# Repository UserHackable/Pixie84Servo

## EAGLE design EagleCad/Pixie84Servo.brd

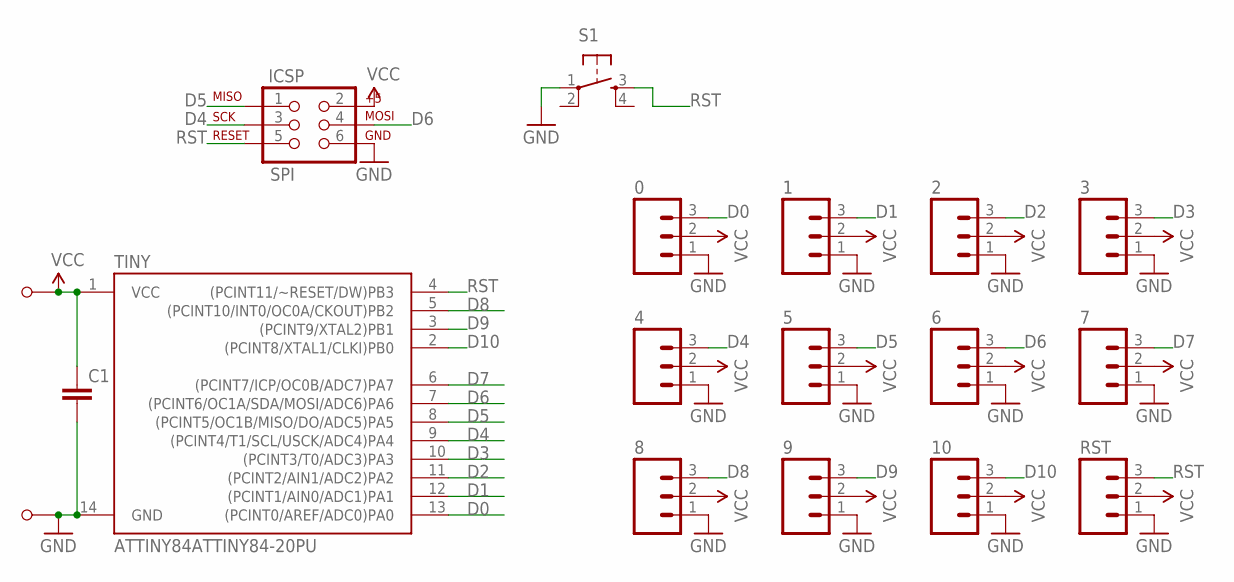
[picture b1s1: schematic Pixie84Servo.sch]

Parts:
0, 1, 2, 3, 4, 5, 6, 7, 8, 9, 10: M03PTH; 1X03
C1: CAPPTH; CAP-PTH-SMALL
ICSP: SPI; 2X3-NS
RST: M03PTH; 1X03
S1: TAC_SWITCHPTH; TACTILE-PTH
TINY: ATTINY84ATTINY84-20PU; DIL14
U$1, U$2: M1; M1_NO_STRAIN

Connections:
D0: 0.3, TINY.13 ((PCINT0/AREF/ADC0)PA0)
D1: 1.3, TINY.12 ((PCINT1/AIN0/ADC1)PA1)
D2: 2.3, TINY.11 ((PCINT2/AIN1/ADC2)PA2)
D3: 3.3, TINY.10 ((PCINT3/T0/ADC3)PA3)
D4: 4.3, ICSP.3 (SCK), TINY.9 ((PCINT4/T1/SCL/USCK/ADC4)PA4)
D5: 5.3, ICSP.1 (MISO), TINY.8 ((PCINT5/OC1B/MISO/DO/ADC5)PA5)
D6: 6.3, ICSP.4 (MOSI), TINY.7 ((PCINT6/OC1A/SDA/MOSI/ADC6)PA6)
D7: 7.3, TINY.6 ((PCINT7/ICP/OC0B/ADC7)PA7)
D8: 8.3, TINY.5 ((PCINT10/INT0/OC0A/CKOUT)PB2)
D9: 9.3, TINY.3 ((PCINT9/XTAL2)PB1)
D10: 10.3, TINY.2 ((PCINT8/XTAL1/CLKI)PB0)
GND: 0.1, 1.1, 2.1, 3.1, 4.1, 5.1, 6.1, 7.1, 8.1, 9.1, 10.1, C1.2, ICSP.6 (GND), RST.1, S1.1, TINY.14 (GND), U$2.P$1
RST: ICSP.5 (RST), RST.3, S1.3, TINY.4 ((PCINT11/~RESET/DW)PB3)
VCC: 0.2, 1.2, 2.2, 3.2, 4.2, 5.2, 6.2, 7.2, 8.2, 9.2, 10.2, C1.1, ICSP.2 (V+), RST.2, TINY.1 (VCC), U$1.P$1

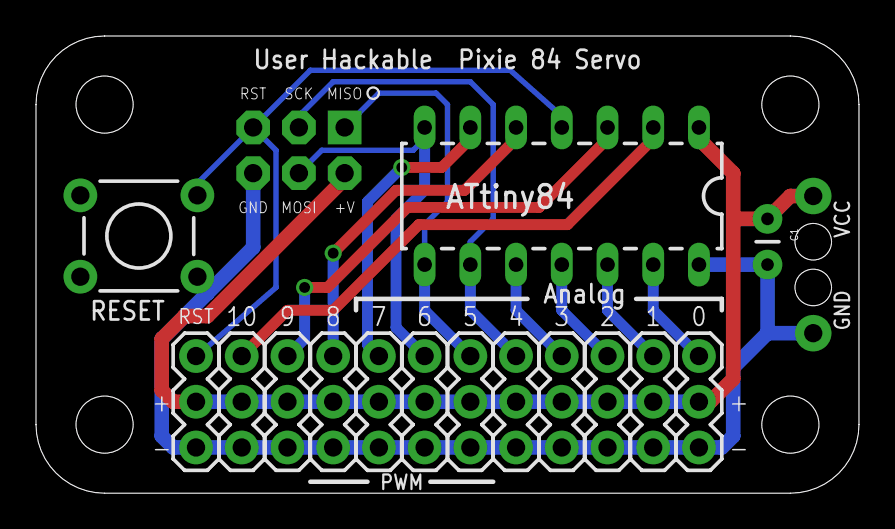
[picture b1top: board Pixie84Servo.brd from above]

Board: 2 copper layers, 45.7 x 25.4 mm, 18 parts (0 on the bottom side), 14 nets.

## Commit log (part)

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2016-04-06 updating makefile
2016-04-06 clearing out gerbers
2016-04-07 from Makefile

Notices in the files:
parts and their libraries:
SparkFun-DigitalIC: Licensing: Creative Commons ShareAlike 4.0 International - https://creativecommons.org/licenses/by-sa/4.0
